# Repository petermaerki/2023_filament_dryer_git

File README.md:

# 2023_filament_dryer

This page is explains the physical aspects.

These topics are not covered:
* Open Hardware and Open Software...
* How to build
* User Guide
* How to run grafana etc.

## Introduction

This filament dryer is used to dry 3D printer filament.

A plastic box (Aliexpress, Kingroon, USD23) is equiped with a dryer module. The module is pluged to USB power (5V, 1A max). The dryer contains about 10g of dried silicagel. A fan blows dry air around the filament. The silicagel will be automatically regenerated when saturated with water: its heated up and the wet air is blown to the enviroment.
It takes about 5 days to dry 1 kg of 1.75 mm filament.

The filament roll is held by a spindle with ballbearings. 

## Drying process

Three rolls of filament are placed in filament_dryers. PLA, PETG and TPU. The rolls have been laying around in my workshop for a long time and therefore I assume they are equally "wet". The filament_dryer is pluged in and I measure the weight of the hole dryer box over the next two weeks.
In the diagramm I show the weight reduction relative to the filament weight (1 kg for example).

Filament types
* PLA	Pink	PLA 1.75 mm 102468 Purefil 1kg
* PETG	dunkelblau	PETG 1.75 mm 102478 Purefil 1 kg
* TPU	blau_transparent	TPU 1.75 mm LOT 20221216 Aliexpress 0.5 kg

### Conclusion

* All of the tested Filaments loose about 3 gramm water per kg filament over a week. I assume the water content after a week is low and perfect for printing.
* The fluctuation of the weight after day 6 is not a measuring error. It is due to the regeneration cycle of the dryer. Water goes into the dry box through the plastic walls or air gaps and gets out through the regenation cycle every few days.

### Drying details

As an example the details of the drying over two weeks are shown.
I do show the absolute water content of the air in g per kg of air. 1 kg air corresponds to about 1 m3 air. The absolute humidity does not depend on temperature and after playing around with different himidity units for a long time, I decided to prefer this unit.

The humidity of the air around the filament changes from 12 g/kg at the start (the filament was laying around in my workshop at this himidity, ambient) to 4 g/kg after one week.

The relative humidity in my workshop is in the range of 60%. The relative humidity of the air arount the filament is decreased down to below 20%.

One cycle of regeneration and drying.

The decision how to proceed is made due to changes of measurenents. If we only observe changes we are not sensitive to measurements errors/offsets. 

# Grafana
It is possible to log to grafana.
[Example](http://www.maerki.com:3000/goto/Yx-3weXSR?orgId=1)

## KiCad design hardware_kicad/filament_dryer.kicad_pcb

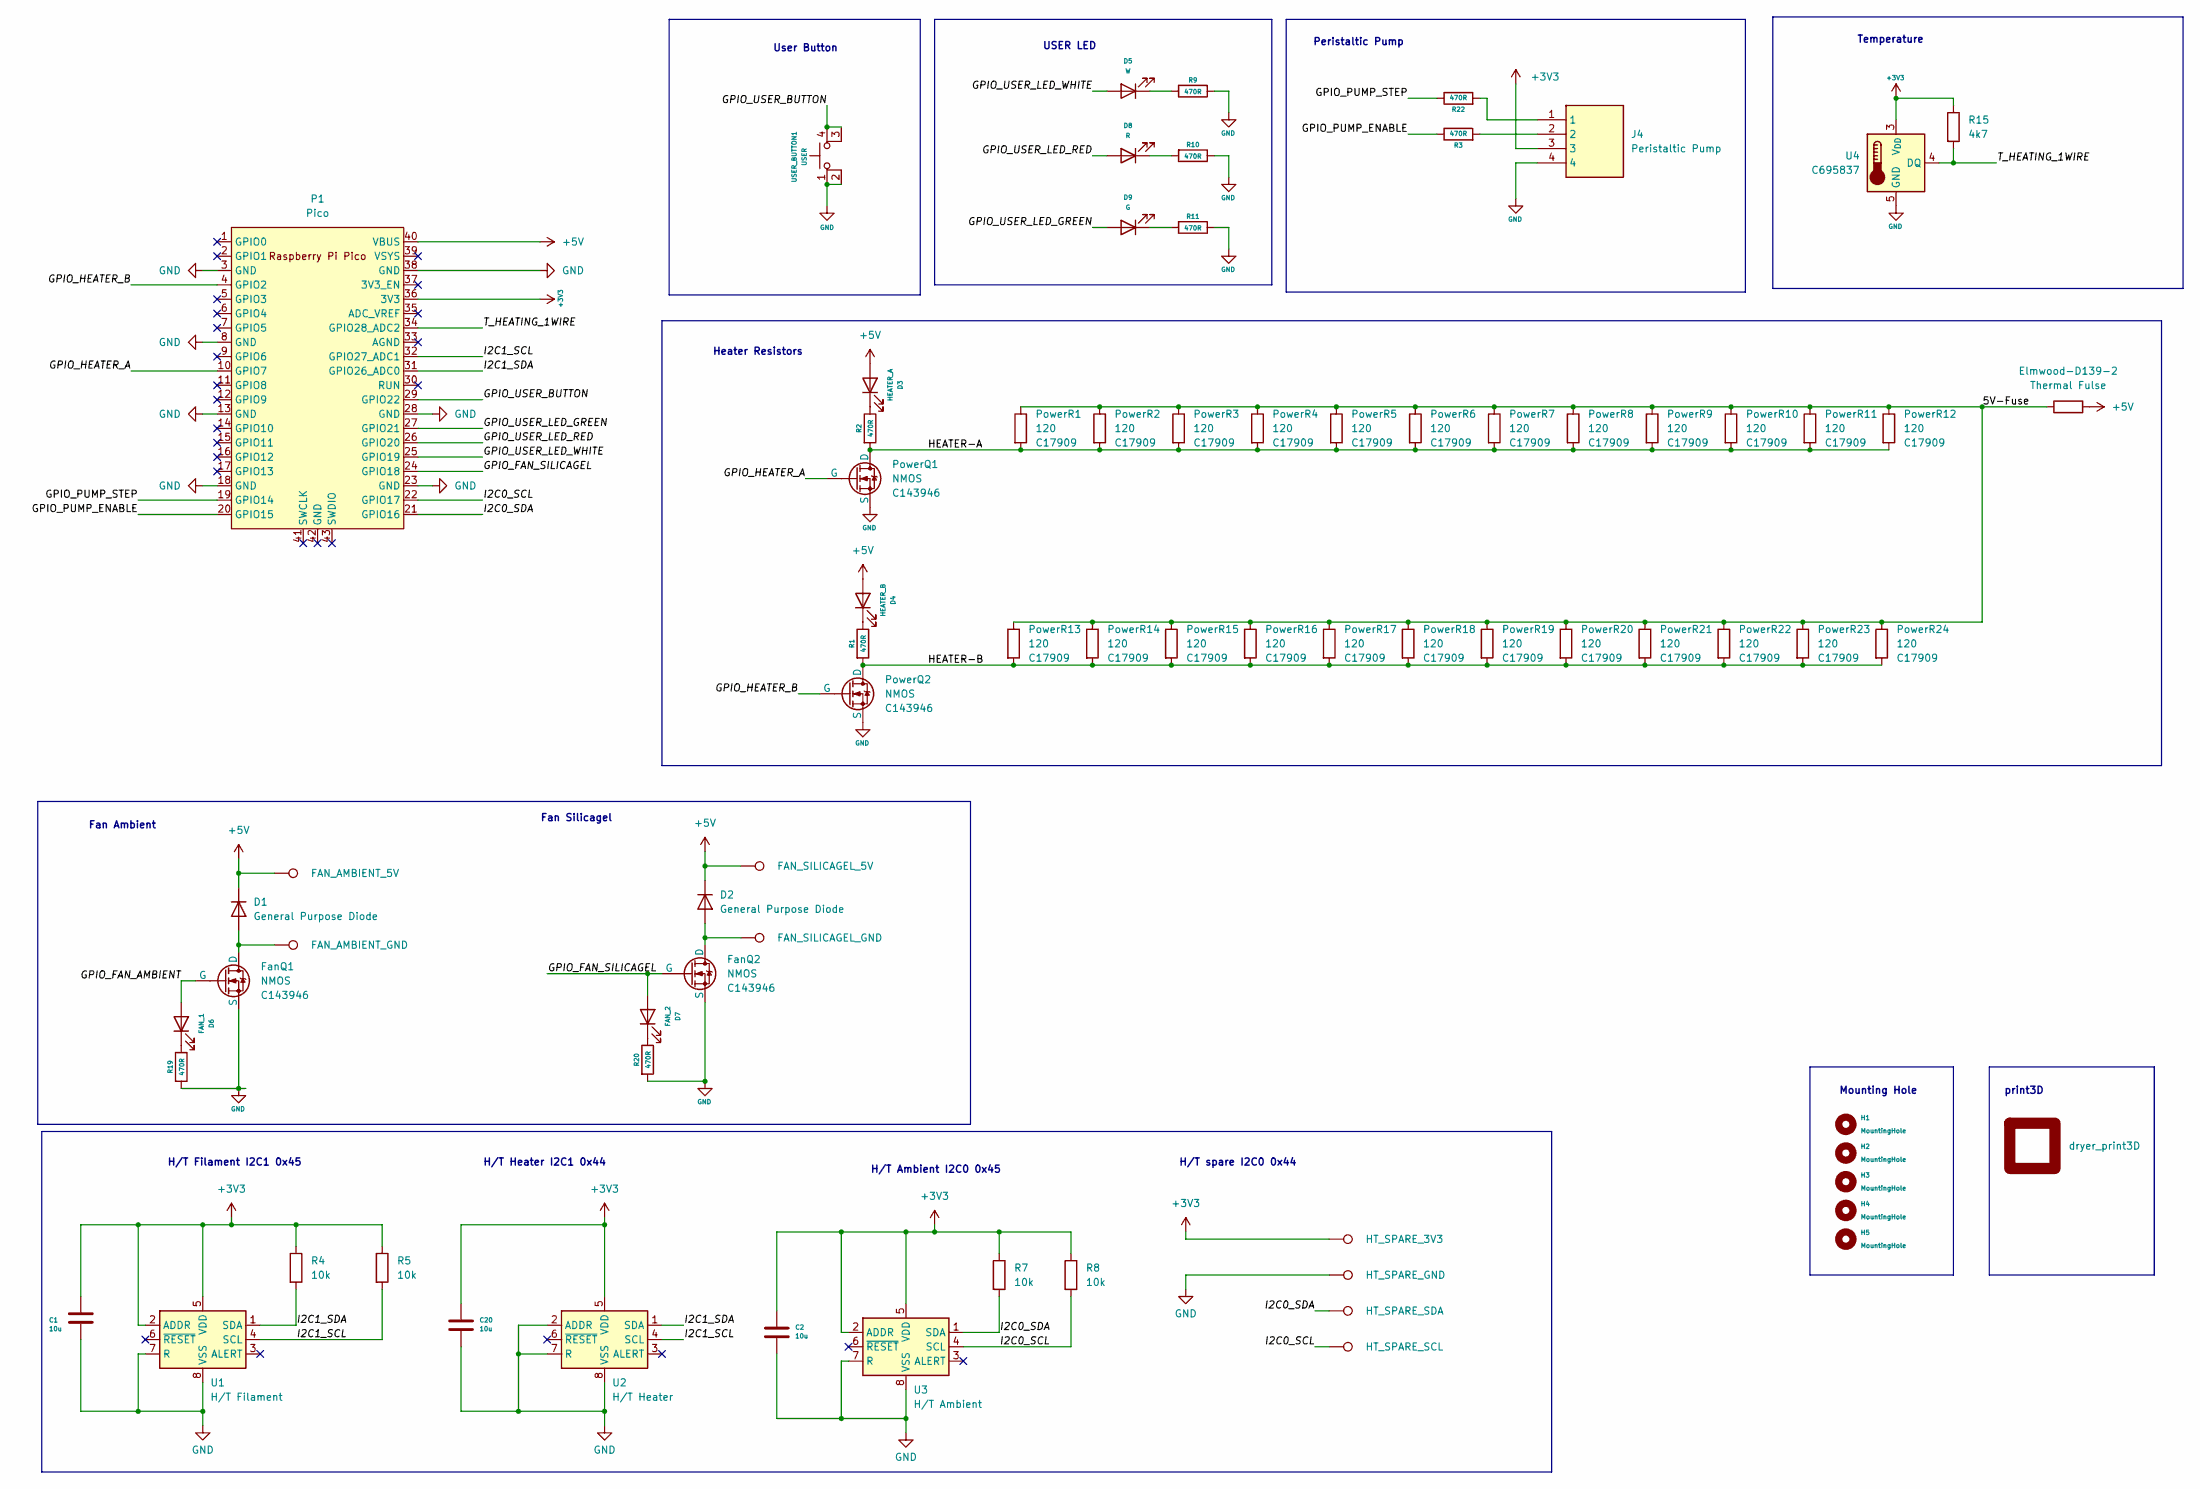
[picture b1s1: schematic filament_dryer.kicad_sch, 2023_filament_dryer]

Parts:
C1, C2: 10u; C_0603_1608Metric; JLC C96446
C20: 10u; C_0603_1608Metric
D1, D2: General Purpose Diode; D_SMA; JLC Part C95872
D3: HEATER_A; LED_0603_1608Metric; JLC C2286
D4: HEATER_B; LED_0603_1608Metric; JLC C2286
D5: W; LED_0603_1608Metric; JLC C2290
D6: FAN_1; LED_0603_1608Metric; JLC C2286
D7: FAN_2; LED_0603_1608Metric; JLC C2286
D8: R; LED_0603_1608Metric; JLC C2286
D9: G; LED_0603_1608Metric; JLC C2297
Elmwood-D139-2: Thermal Fulse; Thermal Fuse (R_Axial_Power_L25.0mm_W6.4mm_P27.94mm)
FanQ1, FanQ2: NMOS; SOT-23; JLC Part C143946
H1, H2, H3, H4, H5: MountingHole; MountingHole_3.2mm_M3
J4: Peristaltic Pump; grove_vert_holes; Mouser Part Number 713-110990030
P1: Pico; RPi_Pico
PowerQ1, PowerQ2: NMOS; SOT-23; JLC Part C143946
PowerR1, PowerR2, PowerR3, PowerR4, PowerR5, PowerR6, PowerR7, PowerR8, PowerR9, PowerR10, PowerR11, PowerR12, PowerR13, PowerR14, PowerR15, PowerR16, PowerR17, PowerR18, PowerR19, PowerR20, PowerR21, PowerR22, PowerR23, PowerR24: 120; R_1206_3216Metric; JLC Part C17909
R1, R2, R3, R9, R10, R11, R19, R20, R22: 470R; R_0402_1005Metric_Pad0.72x0.64mm_HandSolder
R4, R5, R7, R8: 10k; R_0402_1005Metric_Pad0.72x0.64mm_HandSolder
R15: 4k7; R_0402_1005Metric_Pad0.72x0.64mm_HandSolder
TP2: HT_SPARE_GND; TestPoint_Pad_D3.0mm
TP3: HT_SPARE_3V3; TestPoint_Pad_D3.0mm
TP6: HT_SPARE_SDA; TestPoint_Pad_D3.0mm
TP7: FAN_AMBIENT_5V; TestPoint_Pad_D3.0mm
TP8: FAN_AMBIENT_GND; TestPoint_Pad_D3.0mm
TP9: FAN_SILICAGEL_5V; TestPoint_Pad_D3.0mm
TP10: FAN_SILICAGEL_GND; TestPoint_Pad_D3.0mm
TP11: HT_SPARE_SCL; TestPoint_Pad_D3.0mm
U1: H/T Filament; SON50P250X250X90-9T110X180N; JLC C80862
U2: H/T Heater; SON50P250X250X90-9T110X180N; JLC C80862
U3: H/T Ambient; SON50P250X250X90-9T110X180N; JLC C80862
U4: DS18B20Z; SOIC-8_3.9x4.9mm_P1.27mm; JLC Part C695837
USER_BUTTON1: USER; SW_TS-1187A-B-A-B; JLC C318884
dryer_print3D1: dryer_print3D; dryer_print3d

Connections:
+3V3: C1.1, C2.1, C20.1, J4.3, P1.36 (3V3), R4.1, R5.1, R7.1, R8.1, R15.1, TP3.1, U1.2 (ADDR), U1.5 (VDD), U2.5 (VDD), U3.2 (ADDR), U3.5 (VDD), U4.3 (V_{DD})
+5V: D1.1 (K), D2.1 (K), D3.2 (A), D4.2 (A), Elmwood-D139-2.2, P1.40 (VBUS), TP7.1, TP9.1
/5V-Fuse: Elmwood-D139-2.1, PowerR1.1, PowerR2.1, PowerR3.1, PowerR4.1, PowerR5.1, PowerR6.1, PowerR7.1, PowerR8.1, PowerR9.1, PowerR10.1, PowerR11.1, PowerR12.1, PowerR13.1, PowerR14.1, PowerR15.1, PowerR16.1, PowerR17.1, PowerR18.1, PowerR19.1, PowerR20.1, PowerR21.1, PowerR22.1, PowerR23.1, PowerR24.1
/GPIO_FAN_AMBIENT: D6.2 (A), FanQ1.1 (G)
/GPIO_FAN_SILICAGEL: D7.2 (A), FanQ2.1 (G), P1.24 (GPIO18)
/GPIO_HEATER_A: P1.10 (GPIO7), PowerQ1.1 (G)
/GPIO_HEATER_B: P1.4 (GPIO2), PowerQ2.1 (G)
/GPIO_PUMP_ENABLE: P1.20 (GPIO15), R3.1
/GPIO_PUMP_STEP: P1.19 (GPIO14), R22.1
/GPIO_USER_BUTTON: P1.29 (GPIO22), USER_BUTTON1.3 (K), USER_BUTTON1.4 (A)
/GPIO_USER_LED_GREEN: D9.2 (A), P1.27 (GPIO21)
/GPIO_USER_LED_RED: D8.2 (A), P1.26 (GPIO20)
/GPIO_USER_LED_WHITE: D5.2 (A), P1.25 (GPIO19)
/HEATER-A: PowerQ1.3 (D), PowerR1.2, PowerR2.2, PowerR3.2, PowerR4.2, PowerR5.2, PowerR6.2, PowerR7.2, PowerR8.2, PowerR9.2, PowerR10.2, PowerR11.2, PowerR12.2, R2.2
/HEATER-B: PowerQ2.3 (D), PowerR13.2, PowerR14.2, PowerR15.2, PowerR16.2, PowerR17.2, PowerR18.2, PowerR19.2, PowerR20.2, PowerR21.2, PowerR22.2, PowerR23.2, PowerR24.2, R1.2
/I2C0_SCL: P1.22 (GPIO17), R8.2, TP11.1, U3.4 (SCL)
/I2C0_SDA: P1.21 (GPIO16), R7.2, TP6.1, U3.1 (SDA)
/I2C1_SCL: P1.32 (GPIO27_ADC1), R5.2, U1.4 (SCL), U2.4 (SCL)
/I2C1_SDA: P1.31 (GPIO26_ADC0), R4.2, U1.1 (SDA), U2.1 (SDA)
/T_HEATING_1WIRE: P1.34 (GPIO28_ADC2), R15.2, U4.4 (DQ)
GND: C1.2, C2.2, C20.2, FanQ1.2 (S), FanQ2.2 (S), J4.4, P1.3 (GND), P1.8 (GND), P1.13 (GND), P1.18 (GND), P1.23 (GND), P1.28 (GND), P1.38 (GND), PowerQ1.2 (S), PowerQ2.2 (S), R9.1, R10.1, R11.1, R19.2, R20.2, TP2.1, U1.7 (R), U1.8 (VSS), U1.9 (VSS), U2.2 (ADDR), U2.7 (R), U2.8 (VSS), U2.9 (VSS), U3.7 (R), U3.8 (VSS), U3.9 (VSS), U4.5 (GND), USER_BUTTON1.1, USER_BUTTON1.2
unnamed: D1.2 (A), FanQ1.3 (D), TP8.1
unnamed: D2.2 (A), FanQ2.3 (D), TP10.1
unnamed: D3.1 (K), R2.1
unnamed: D4.1 (K), R1.1
unnamed: D5.1 (K), R9.2
unnamed: D6.1 (K), R19.1
unnamed: D7.1 (K), R20.1
unnamed: D8.1 (K), R10.2
unnamed: D9.1 (K), R11.2
unnamed: J4.1, R22.2
unnamed: J4.2, R3.2

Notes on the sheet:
Peristaltic Pump
Mounting Hole
User Button
USER LED
H/T Ambient I2C0 0x45
H/T spare I2C0 0x44
Fan Silicagel
Heater Resistors
print3D
Fan Ambient
Temperature
H/T Heater I2C1 0x44
H/T Filament I2C1 0x45

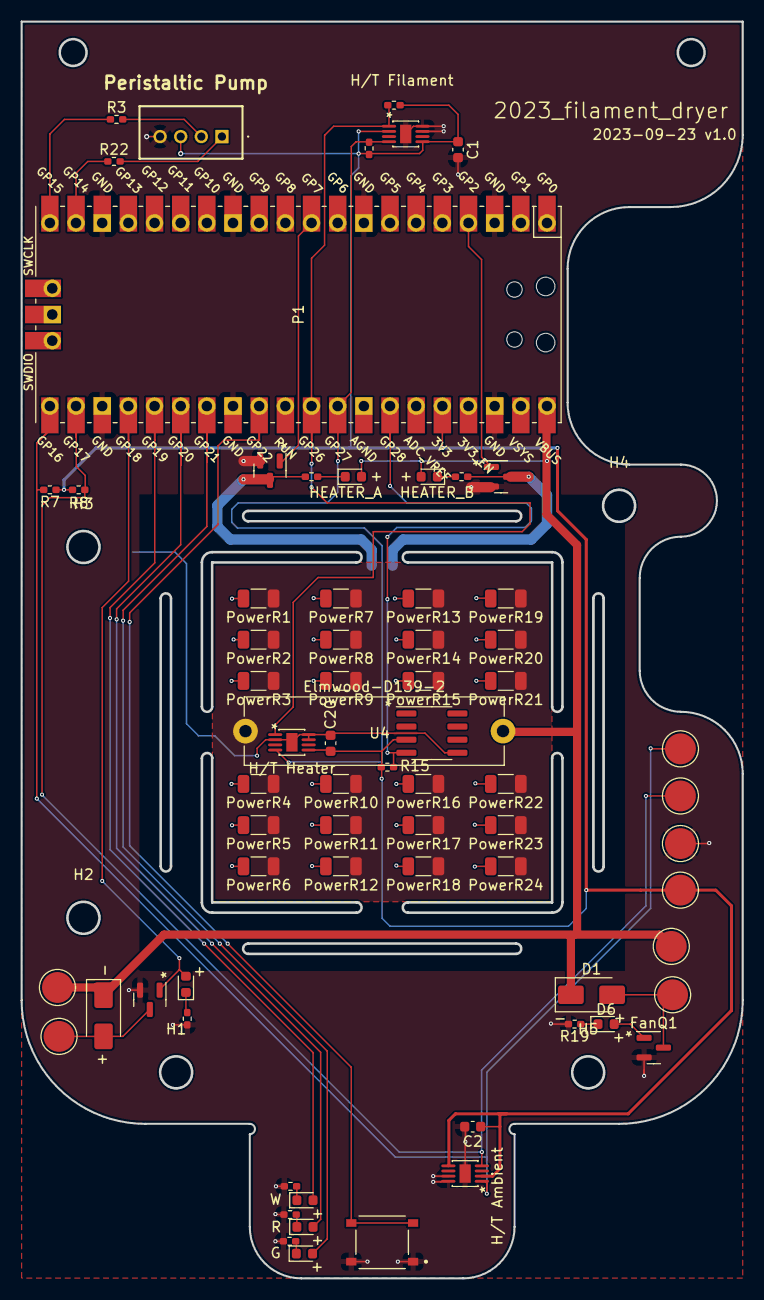
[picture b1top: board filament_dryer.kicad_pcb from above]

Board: 2 copper layers, 70.0 x 122.0 mm, 76 parts (0 on the bottom side), 32 nets.

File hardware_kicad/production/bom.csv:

Designator,Footprint,Quantity,Value,LCSC Part #
"C1, C2, C20",0603,3,10u,C96446
"D1, D2",D_SMA,2,General Purpose Diode,C95872
D3,0603,1,HEATER_A,C2286
D4,0603,1,HEATER_B,C2286
D5,0603,1,W,C2290
D6,0603,1,FAN_1,C2286
D7,0603,1,FAN_2,C2286
D8,0603,1,R,C2286
D9,0603,1,G,C2297
"FanQ1, FanQ2, PowerQ1, PowerQ2",SOT-23,4,NMOS,C143946
"H1, H2, H3, H4, H5",MountingHole_3.2mm_M3,5,MountingHole,
"PowerR1, PowerR10, PowerR11, PowerR12, PowerR13, PowerR14, PowerR15, PowerR16, PowerR17, PowerR18, PowerR19, PowerR2, PowerR20, PowerR21, PowerR22, PowerR23, PowerR24, PowerR3, PowerR4, PowerR5, PowerR6, PowerR7, PowerR8, PowerR9",1206,24,120,C17909
"R1, R10, R11, R19, R2, R20, R22, R3, R9",0402,9,470R,
R15,0402,1,4k7,
"R4, R5, R7, R8",0402,4,10k,
TP10,TestPoint_Pad_D3.0mm,1,FAN_SILICAGEL_GND,
TP11,TestPoint_Pad_D3.0mm,1,HT_SPARE_SCL,
TP2,TestPoint_Pad_D3.0mm,1,HT_SPARE_GND,
TP3,TestPoint_Pad_D3.0mm,1,HT_SPARE_3V3,
TP6,TestPoint_Pad_D3.0mm,1,HT_SPARE_SDA,
TP7,TestPoint_Pad_D3.0mm,1,FAN_AMBIENT_5V,
TP8,TestPoint_Pad_D3.0mm,1,FAN_AMBIENT_GND,
TP9,TestPoint_Pad_D3.0mm,1,FAN_SILICAGEL_5V,
U1,SON50P250X250X90-9T110X180N,1,H/T Filament,C80862
U2,SON50P250X250X90-9T110X180N,1,H/T Heater,C80862
U3,SON50P250X250X90-9T110X180N,1,H/T Ambient,C80862
U4,SOIC-8_3.9x4.9mm_P1.27mm,1,DS18B20Z,C695837
USER_BUTTON1,SW_TS-1187A-B-A-B,1,USER,C318884

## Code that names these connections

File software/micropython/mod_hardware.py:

from machine import Pin, I2C
import time

import config


class Heater:
    def __init__(self, hardware: "Hardware"):
        self._power = False
        self._board_C = 0.0
        self._hardware = hardware
        self.write_power()

    @property
    def power_controlled(self) -> bool:
        if self._board_C > config.HEATER_BOARD_MAX_C:
            return False
        return self._power

    def set_power(self, power: bool):
        self._power = power

        self.write_power()

    def set_board_C(self, board_C: int):
        self._board_C = board_C

        self.write_power()

    def write_power(self) -> None:
        power = self.power_controlled

        self._hardware.PIN_GPIO_HEATER_A.value(power)
        self._hardware.PIN_GPIO_HEATER_B.value(power)


class Hardware:
    def __init__(self):
        self.PIN_GPIO_BUTTON = Pin("GPIO22", mode=Pin.IN, pull=Pin.PULL_UP)
        self.PIN_GPIO_LED_GREEN = Pin("GPIO21", mode=Pin.OUT, value=0)
        self.PIN_GPIO_LED_RED = Pin("GPIO20", mode=Pin.OUT, value=0)
        self.PIN_GPIO_LED_WHITE = Pin("GPIO19", mode=Pin.OUT, value=0)

        self.PIN_GPIO_HEATER_A = Pin("GPIO7", mode=Pin.OUT, value=0)
        self.PIN_GPIO_HEATER_B = Pin("GPIO2", mode=Pin.OUT, value=0)

        self.PIN_GPIO_FAN_AMBIENT = Pin("GPIO5", mode=Pin.OUT, value=0)  # vorher 0
        self.PIN_GPIO_FAN_FILAMENT = Pin("GPIO18", mode=Pin.OUT, value=0)
        self.PIN_GPIO_FAN_BOX = Pin("GPIO4", mode=Pin.OUT, value=0)

        self.i2c0 = I2C(id=0, scl=Pin("GPIO17"), sda=Pin("GPIO16"), freq=400000)
        self.i2c1 = I2C(id=1, scl=Pin("GPIO27"), sda=Pin("GPIO26"), freq=400000)
        self.heater = Heater(self)

    def led_toggle(self) -> None:
        self.PIN_GPIO_LED_GREEN.toggle()
        self.PIN_GPIO_LED_RED.toggle()
        self.PIN_GPIO_LED_WHITE.toggle()

    def production_test(self, wdt_feed_cb):
        # Neue prints testen
        while True:
            for name, pin in (
                ("led g", self.PIN_GPIO_LED_GREEN),
                ("led r", self.PIN_GPIO_LED_RED),
                ("led w", self.PIN_GPIO_LED_WHITE),
                ("fan silicagel", self.PIN_GPIO_FAN_FILAMENT),
                ("heater a", self.PIN_GPIO_HEATER_A),
                ("heater b", self.PIN_GPIO_HEATER_B),
                ("fan silicagel", self.PIN_GPIO_FAN_BOX),
                ("fan ambient", self.PIN_GPIO_FAN_AMBIENT),
            ):
                print(name)
                pin.value(1)
                time.sleep(2)
                pin.value(0)
                wdt_feed_cb()

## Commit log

2023-07-09 Import hardware_kicad
2023-07-09 Cleanup Schema
2023-07-09 First experiments
2023-08-12 hardware_kicad v0.5
2023-08-12 Add dryer_print3d footprint and pcb
2023-08-13 Added new parts
2023-08-13 Some more layout
2023-08-19 Update 3d footprint
2023-08-19 routing
2023-08-20 2023-08-20 review schematics
2023-08-20 Removed resistors, add locked zones
2023-08-20 Last version with resistors
2023-08-21 Ready for second review
2023-08-21 Remove 4 diodes
2023-08-21 After second review
2023-08-22 After second review 2
2023-08-22 hardware_kicad v0.6
2023-08-26 persitaltic_pump
2023-09-04 lib_drv8825.py
2023-09-05 refactor
2023-09-06 Successful test on board v0.6
2023-09-08 images
2023-09-10 2023-09-10b_logdata
2023-09-11 2023-09-11a_logdata.txt
2023-09-11 2023-09-11b_logdata
2023-09-11 run_diagram.py
2023-09-12 2023-09-11c_logdata
2023-09-12 Abbruchkriterium '_state_dryfan'
2023-09-12 2023-09-12b_logdata.txt
2023-09-12 Abbruchkriterium regeneration
2023-09-12 2023-09-12c_logdata.txt
2023-09-13 2023-09-12d_logdata.svg
2023-09-13 Improve diagram
2023-09-14 2023-09-12g_logdata.svg
2023-09-16 2023-09-16c_logdata.txt
2023-09-16 drayer_print_3d -> dryer_print_3d
2023-09-17 2023-09-17a_logdata
2023-09-17 schematics
2023-09-17 2023-09-17b_logdata.txt
2023-09-17 20230917p_filament_dryer_silicagel.FCStd
2023-09-18 umqtt sample
2023-09-18 schematics ready for review
2023-09-19 board outline cleaned up
2023-09-19 2023-09-19a_logdata.txt
2023-09-19 layouting
2023-09-20 update dxf footprint print3d
2023-09-22 2023-09-22a_logdata
2023-09-22 Preparation for review
2023-09-22 Remove library circuitstate
2023-09-22 fet renumbered
2023-09-23 v1.0
2023-09-29 Versuche MQTT
2023-09-29 Update micropython code
2023-09-30 Strage behaviour when running in thread...
2023-09-30 Add mqtt callbacks
2023-09-30 mqtt authentication
2023-09-30 Add secretes for www.maerki.com
2023-09-30 First tries @ hombi
2023-09-30 Button
2023-09-30 Status LEDs
2023-09-30 With grafana annotations
2023-10-01 Fixes mit Peter
2023-10-02 Adjust.
2023-10-03 Faster.
2023-10-05 big refactoring
2023-10-05 big refactoring 4
2023-10-05 small fixes
2023-10-05 big refactoring 2
2023-10-05 big refactoring 3
2023-10-05 New: uptime_h
2023-10-19 big refactoring 5
2023-10-20 v1.1 PCB
2023-10-21 Hans versuche wdt cores
2023-10-21 Enhances utils_wlan.py a lot
2023-10-21 Cleaning up mqtt annotations
2023-10-21 Erweiterungen Peter
2023-10-21 production test
2023-10-21 heater_C
2023-11-17 New: app_packager.py
2023-11-17 heating only if dewpoint of heater low enough
2023-11-17 Leiterplatte GPIO 1.1
2023-11-17 Fixes
2023-11-17 Add config_secrets-hans.py.gpg
2023-11-18 Allow ctrl-c to disable watchdog
2023-12-08 Butten press while power on: disable watchdog
2024-01-17 Button press while power on: disable watchdog
2024-01-17 Toggle LEDs while measuring the sensors
2024-01-28 cleanup utils_wdt.py
2024-02-15 Fix longterm hanger
2024-05-26 Add README_TODO_software_update.md
2024-05-27 Introduce 'update_success.txt'
2024-06-22 Add freecad files. Cleanup directory structure.
2024-07-28 readme.md

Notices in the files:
hardware_kicad/filament_dryer.kicad_pcb:
Released under MIT Open-source License
